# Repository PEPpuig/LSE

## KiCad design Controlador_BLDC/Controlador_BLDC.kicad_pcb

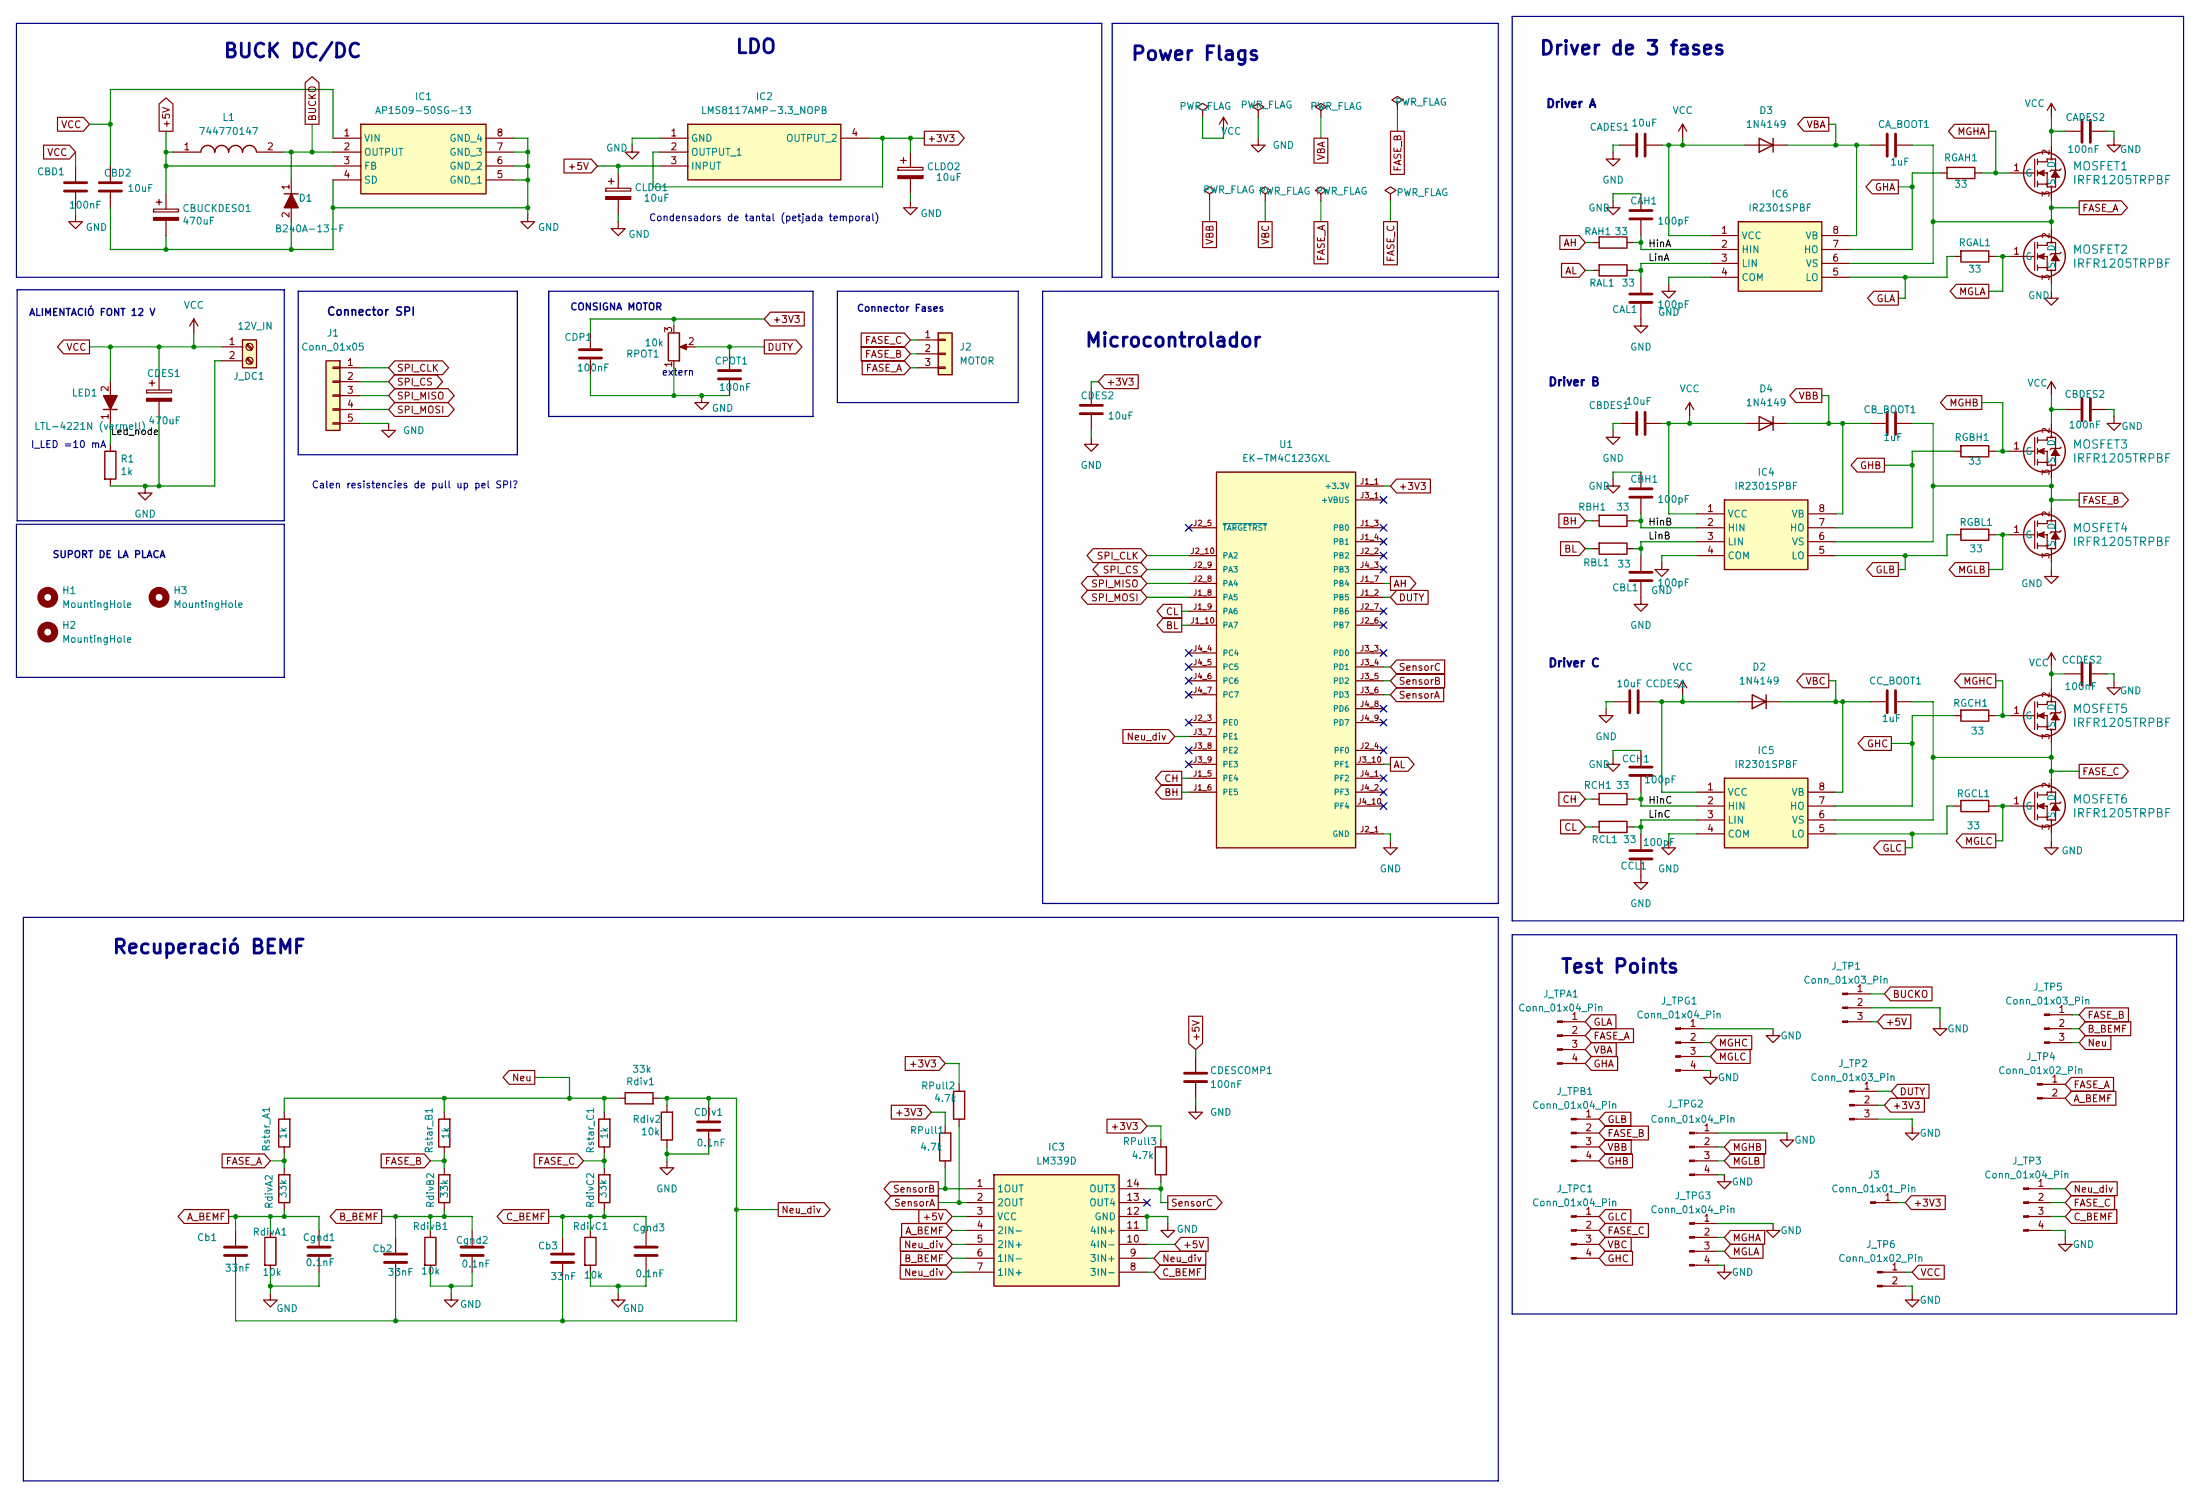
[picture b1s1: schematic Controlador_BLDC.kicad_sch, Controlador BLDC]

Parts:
CADES1: 10uF; C_1206_3216Metric_Pad1.33x1.80mm_HandSolder
CADES2: 100nF; C_1206_3216Metric_Pad1.33x1.80mm_HandSolder
CAH1: 100pF; C_1206_3216Metric_Pad1.33x1.80mm_HandSolder
CAL1: 100pF; C_1206_3216Metric_Pad1.33x1.80mm_HandSolder
CA_BOOT1: 1uF; C_1206_3216Metric_Pad1.33x1.80mm_HandSolder
CBD1: 100nF; C_1206_3216Metric_Pad1.33x1.80mm_HandSolder
CBD2: 10uF; C_1206_3216Metric_Pad1.33x1.80mm_HandSolder
CBDES1: 10uF; C_1206_3216Metric_Pad1.33x1.80mm_HandSolder
CBDES2: 100nF; C_1206_3216Metric_Pad1.33x1.80mm_HandSolder
CBH1: 100pF; C_1206_3216Metric_Pad1.33x1.80mm_HandSolder
CBL1: 100pF; C_1206_3216Metric_Pad1.33x1.80mm_HandSolder
CBUCKDESO1: 470uF; CP_Elec_10x10.5
CB_BOOT1: 1uF; C_1206_3216Metric_Pad1.33x1.80mm_HandSolder
CCDES1: 10uF; C_1206_3216Metric_Pad1.33x1.80mm_HandSolder
CCDES2: 100nF; C_1206_3216Metric_Pad1.33x1.80mm_HandSolder
CCH1: 100pF; C_1206_3216Metric_Pad1.33x1.80mm_HandSolder
CCL1: 100pF; C_1206_3216Metric_Pad1.33x1.80mm_HandSolder
CC_BOOT1: 1uF; C_1206_3216Metric_Pad1.33x1.80mm_HandSolder
CDES1: 470uF; CP_Elec_10x10.5
CDES2: 10uF; C_1206_3216Metric_Pad1.33x1.80mm_HandSolder
CDESCOMP1: 100nF; C_1206_3216Metric_Pad1.33x1.80mm_HandSolder
CDP1: 100nF; C_1206_3216Metric_Pad1.33x1.80mm_HandSolder
CDiv1: 0.1nF; C_1206_3216Metric_Pad1.33x1.80mm_HandSolder
CLDO1, CLDO2: 10uF; CP_EIA-2012-12_Kemet-R
CPOT1: 100nF; C_1206_3216Metric_Pad1.33x1.80mm_HandSolder
Cb1, Cb2, Cb3: 33nF; C_1206_3216Metric_Pad1.33x1.80mm_HandSolder
Cgnd1, Cgnd2, Cgnd3: 0.1nF; C_1206_3216Metric_Pad1.33x1.80mm_HandSolder
D1: B240A-13-F; DIOM5226X230N; Mouser Part Number 621-B240A-F
D2, D3, D4: 1N4149; D_DO-35_SOD27_P7.62mm_Horizontal
H1, H2, H3: MountingHole; MountingHole_3.2mm_M3
IC1: AP1509-50SG-13; SOIC127P600X170-8N; Manufacturer_Part_Number AP1509-50SG-13; Mouser Part Number 621-AP1509-50SG-13
IC2: LMS8117AMP-3.3_NOPB; SOT230P700X180-4N; Mouser Part Number 926-LMS8117AMP33NOPB
IC3: LM339D; SOIC127P600X175-14N; Mouser Part Number 595-LM339D
IC4, IC5, IC6: IR2301SPBF; SOIC127P600X175-8N; Mouser Part Number 942-IR2301SPBF
J1: Conn_01x05; PinHeader_1x05_P2.54mm_Vertical
J2: MOTOR; TerminalBlock_Phoenix_MKDS-1,5-3-5.08_1x03_P5.08mm_Horizont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
J3: Conn_01x01_Pin; PinHeader_1x01_P2.54mm_Vertical
J_DC1: 12V_IN; TerminalBlock_Phoenix_MKDS-1,5-2-5.08_1x02_P5.08mm_Horizont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
J_TP1, J_TP2, J_TP5: Conn_01x03_Pin; PinHeader_1x03_P2.54mm_Vertical
J_TP3: Conn_01x04_Pin; PinHeader_1x04_P2.54mm_Vertical
J_TP4, J_TP6: Conn_01x02_Pin; PinHeader_1x02_P2.54mm_Vertical
J_TPA1: Conn_01x04_Pin; PinHeader_1x04_P2.54mm_Vertical
J_TPB1: Conn_01x04_Pin; PinHeader_1x04_P2.54mm_Vertical
J_TPC1: Conn_01x04_Pin; PinHeader_1x04_P2.54mm_Vertical
J_TPG1, J_TPG2, J_TPG3: Conn_01x04_Pin; PinHeader_1x04_P2.54mm_Vertical
L1: 744770147; WE-PD_1260_1245_1280_121054; Mouser Part Number 710-744770147
LED1: LTL-4221N (vermell); LTL4221N; Mouser Part Number 859-LTL-4221N
MOSFET1, MOSFET2, MOSFET3, MOSFET4, MOSFET5, MOSFET6: IRFR1205TRPBF; D-PAK_TO-252AA_INF
R1: 1k; R_1206_3216Metric_Pad1.30x1.75mm_HandSolder
RAH1: 33; R_1206_3216Metric_Pad1.30x1.75mm_HandSolder
RAL1: 33; R_1206_3216Metric_Pad1.30x1.75mm_HandSolder
RBH1: 33; R_1206_3216Metric_Pad1.30x1.75mm_HandSolder
RBL1: 33; R_1206_3216Metric_Pad1.30x1.75mm_HandSolder
RCH1: 33; R_1206_3216Metric_Pad1.30x1.75mm_HandSolder
RCL1: 33; R_1206_3216Metric_Pad1.30x1.75mm_HandSolder
RGAH1: 33; R_1206_3216Metric_Pad1.30x1.75mm_HandSolder
RGAL1: 33; R_1206_3216Metric_Pad1.30x1.75mm_HandSolder
RGBH1: 33; R_1206_3216Metric_Pad1.30x1.75mm_HandSolder
RGBL1: 33; R_1206_3216Metric_Pad1.30x1.75mm_HandSolder
RGCH1: 33; R_1206_3216Metric_Pad1.30x1.75mm_HandSolder
RGCL1: 33; R_1206_3216Metric_Pad1.30x1.75mm_HandSolder
RPOT1: 10k; TerminalBlock_Phoenix_MKDS-1,5-3-5.08_1x03_P5.08mm_Horizont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
RPull1, RPull2, RPull3: 4.7k; R_1206_3216Metric_Pad1.30x1.75mm_HandSolder
Rdiv1: 33k; R_1206_3216Metric_Pad1.30x1.75mm_HandSolder
Rdiv2: 10k; R_1206_3216Metric_Pad1.30x1.75mm_HandSolder
RdivA1: 10k; R_1206_3216Metric_Pad1.30x1.75mm_HandSolder
RdivA2: 33k; R_1206_3216Metric_Pad1.30x1.75mm_HandSolder
RdivB1: 10k; R_1206_3216Metric_Pad1.30x1.75mm_HandSolder
RdivB2: 33k; R_1206_3216Metric_Pad1.30x1.75mm_HandSolder
RdivC1: 10k; R_1206_3216Metric_Pad1.30x1.75mm_HandSolder
RdivC2: 33k; R_1206_3216Metric_Pad1.30x1.75mm_HandSolder
Rstar_A1: 1k; R_1206_3216Metric_Pad1.30x1.75mm_HandSolder
Rstar_B1: 1k; R_1206_3216Metric_Pad1.30x1.75mm_HandSolder
Rstar_C1: 1k; R_1206_3216Metric_Pad1.30x1.75mm_HandSolder
U1: EK-TM4C123GXL; MODULE_EK-TM4C123GXL_mofied; PARTREV April 2013

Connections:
+3V3: CDES2.1, CDP1.1, CLDO2.1, IC2.2 (OUTPUT_1), IC2.4 (OUTPUT_2), J3.1, J_TP2.2, RPOT1.3, RPull1.2, RPull2.2, RPull3.2, U1.J1_1 (+3.3V)
+5V: CBUCKDESO1.1, CDESCOMP1.1, CLDO1.1, IC1.3 (FB), IC2.3 (INPUT), IC3.3 (VCC), IC3.10 (4IN-), J_TP1.3, L1.1
/HinA: CAH1.2, IC6.2 (HIN), RAH1.1
/HinB: CBH1.2, IC4.2 (HIN), RBH1.1
/HinC: CCH1.2, IC5.2 (HIN), RCH1.1
/Led_node: LED1.1 (K), R1.1
/LinA: CAL1.1, IC6.3 (LIN), RAL1.1
/LinB: CBL1.1, IC4.3 (LIN), RBL1.1
/LinC: CCL1.1, IC5.3 (LIN), RCL1.1
AH: RAH1.2, U1.J1_7 (PB4)
AL: RAL1.2, U1.J3_10 (PF1)
A_BEMF: Cb1.1, Cgnd1.1, IC3.4 (2IN-), J_TP4.2, RdivA1.1, RdivA2.1
BH: RBH1.2, U1.J1_6 (PE5)
BL: RBL1.2, U1.J1_10 (PA7)
BUCKO: D1.1 (K), IC1.2 (OUTPUT), J_TP1.1, L1.2
B_BEMF: Cb2.1, Cgnd2.1, IC3.6 (1IN-), J_TP5.2, RdivB1.1, RdivB2.1
CH: RCH1.2, U1.J1_5 (PE4)
CL: RCL1.2, U1.J1_9 (PA6)
C_BEMF: Cb3.1, Cgnd3.1, IC3.8 (3IN-), J_TP3.3, RdivC1.1, RdivC2.1
DUTY: CPOT1.1, J_TP2.1, RPOT1.2, U1.J1_2 (PB5)
FASE_A: CA_BOOT1.1, IC6.6 (VS), J2.3, J_TP4.1, J_TPA1.2, MOSFET1.3 (S), MOSFET2.2 (D), RdivA2.2, Rstar_A1.1
FASE_B: CB_BOOT1.1, IC4.6 (VS), J2.2, J_TP5.1, J_TPB1.2, MOSFET3.3 (S), MOSFET4.2 (D), RdivB2.2, Rstar_B1.1
FASE_C: CC_BOOT1.1, IC5.6 (VS), J2.1, J_TP3.2, J_TPC1.2, MOSFET5.3 (S), MOSFET6.2 (D), RdivC2.2, Rstar_C1.1
GHA: IC6.7 (HO), J_TPA1.4, RGAH1.2
GHB: IC4.7 (HO), J_TPB1.4, RGBH1.2
GHC: IC5.7 (HO), J_TPC1.4, RGCH1.2
GLA: IC6.5 (LO), J_TPA1.1, RGAL1.2
GLB: IC4.5 (LO), J_TPB1.1, RGBL1.2
GLC: IC5.5 (LO), J_TPC1.1, RGCL1.2
GND: CADES1.1, CADES2.2, CAH1.1, CAL1.2, CBD1.2, CBD2.2, CBDES1.1, CBDES2.2, CBH1.1, CBL1.2, CBUCKDESO1.2, CCDES1.2, CCDES2.2, CCH1.1, CCL1.2, CDES1.2, CDES2.2, CDESCOMP1.2, CDP1.2, CDiv1.2, CLDO1.2, CLDO2.2, CPOT1.2, Cgnd1.2, Cgnd2.2, Cgnd3.2, D1.2 (A), IC1.4 (SD), IC1.5 (GND_1), IC1.6 (GND_2), IC1.7 (GND_3), IC1.8 (GND_4), IC2.1 (GND), IC3.11 (4IN+), IC3.12 (GND), IC4.4 (COM), IC5.4 (COM), IC6.4 (COM), J1.5, J_DC1.2, J_TP1.2, J_TP2.3, J_TP3.4, J_TP6.2, J_TPG1.1, J_TPG1.4, J_TPG2.1, J_TPG2.4, J_TPG3.1, J_TPG3.4, MOSFET2.3 (S), MOSFET4.3 (S), MOSFET6.3 (S), R1.2, RPOT1.1, Rdiv2.1, RdivA1.2, RdivB1.2, RdivC1.2, U1.J2_1 (GND), U1.J3_2 (GND)
MGHA: J_TPG3.2, MOSFET1.1 (G), RGAH1.1
MGHB: J_TPG2.2, MOSFET3.1 (G), RGBH1.1
MGHC: J_TPG1.2, MOSFET5.1 (G), RGCH1.1
MGLA: J_TPG3.3, MOSFET2.1 (G), RGAL1.1
MGLB: J_TPG2.3, MOSFET4.1 (G), RGBL1.1
MGLC: J_TPG1.3, MOSFET6.1 (G), RGCL1.1
Neu: J_TP5.3, Rdiv1.1, Rstar_A1.2, Rstar_B1.2, Rstar_C1.2
Neu_div: CDiv1.1, Cb1.2, Cb2.2, Cb3.2, IC3.5 (2IN+), IC3.7 (1IN+), IC3.9 (3IN+), J_TP3.1, Rdiv1.2, Rdiv2.2, U1.J3_7 (PE1)
SPI_CLK: J1.1, U1.J2_10 (PA2)
SPI_CS: J1.2, U1.J2_9 (PA3)
SPI_MISO: J1.3, U1.J2_8 (PA4)
SPI_MOSI: J1.4, U1.J1_8 (PA5)
SensorA: IC3.2 (2OUT), RPull2.1, U1.J3_6 (PD3)
SensorB: IC3.1 (1OUT), RPull1.1, U1.J3_5 (PD2)
SensorC: IC3.14 (OUT3), RPull3.1, U1.J3_4 (PD1)
VBA: CA_BOOT1.2, D3.1 (K), IC6.8 (VB), J_TPA1.3
VBB: CB_BOOT1.2, D4.1 (K), IC4.8 (VB), J_TPB1.3
VBC: CC_BOOT1.2, D2.1 (K), IC5.8 (VB), J_TPC1.3
VCC: CADES1.2, CADES2.1, CBD1.1, CBD2.1, CBDES1.2, CBDES2.1, CCDES1.1, CCDES2.1, CDES1.1, D2.2 (A), D3.2 (A), D4.2 (A), IC1.1 (VIN), IC4.1 (VCC), IC5.1 (VCC), IC6.1 (VCC), J_DC1.1, J_TP6.1, LED1.2 (A), MOSFET1.2 (D), MOSFET3.2 (D), MOSFET5.2 (D)

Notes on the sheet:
I_LED =10 mA
Driver C
BUCK DC/DC
LDO
Calen resistencies de pull up pel SPI?
Connector Fases
Condensadors de tantal (petjada temporal)
Test Points
Driver de 3 fases
Driver A
Connector SPI
Recuperació BEMF
Driver B
Microcontrolador
ALIMENTACIÓ FONT 12 V
CONSIGNA MOTOR
extern
Power Flags
SUPORT DE LA PLACA

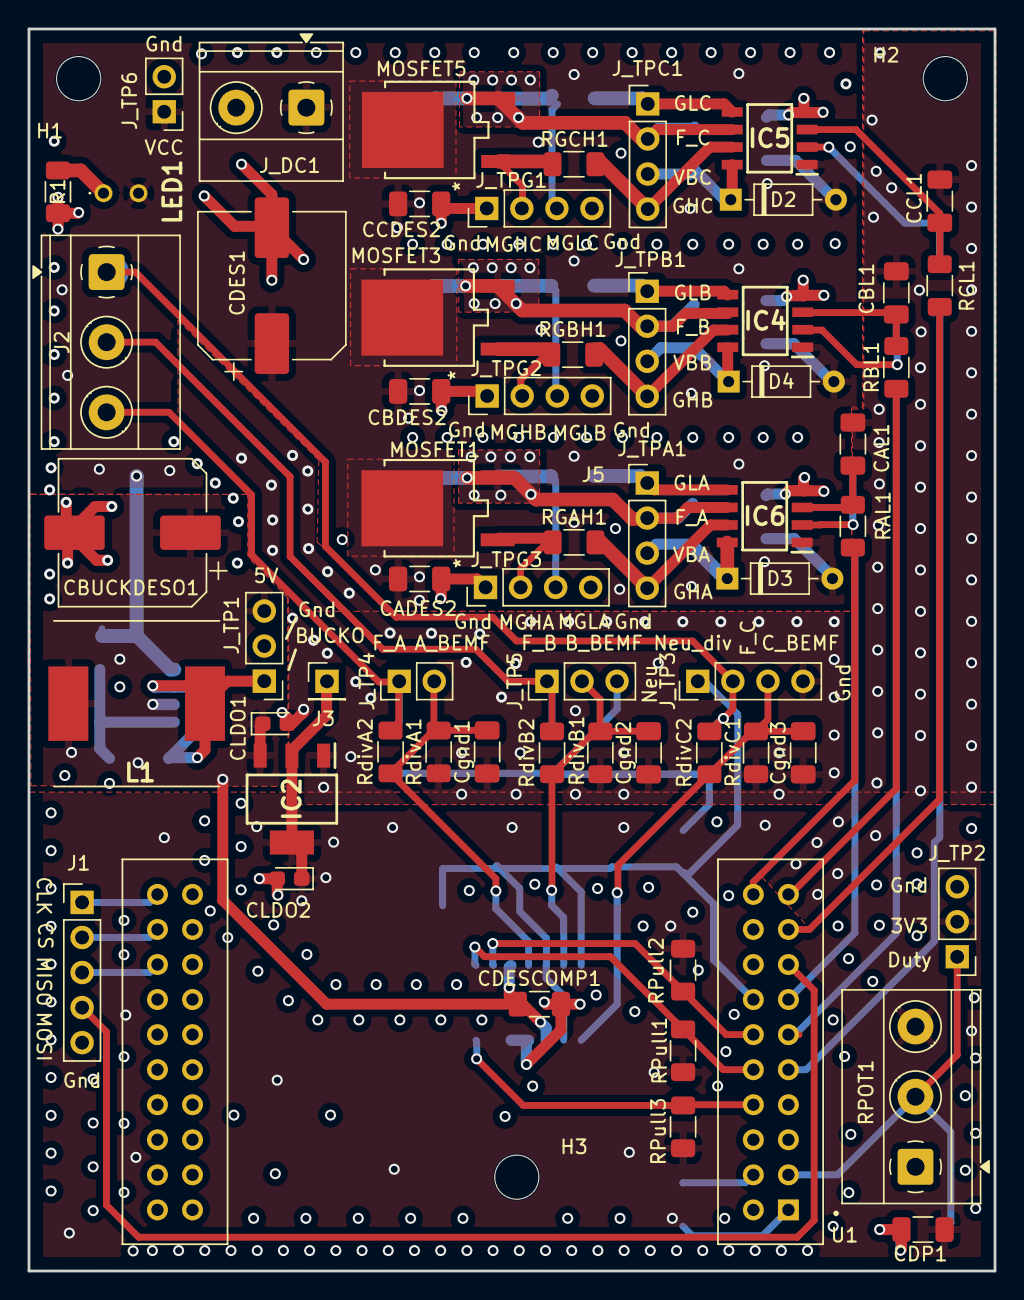
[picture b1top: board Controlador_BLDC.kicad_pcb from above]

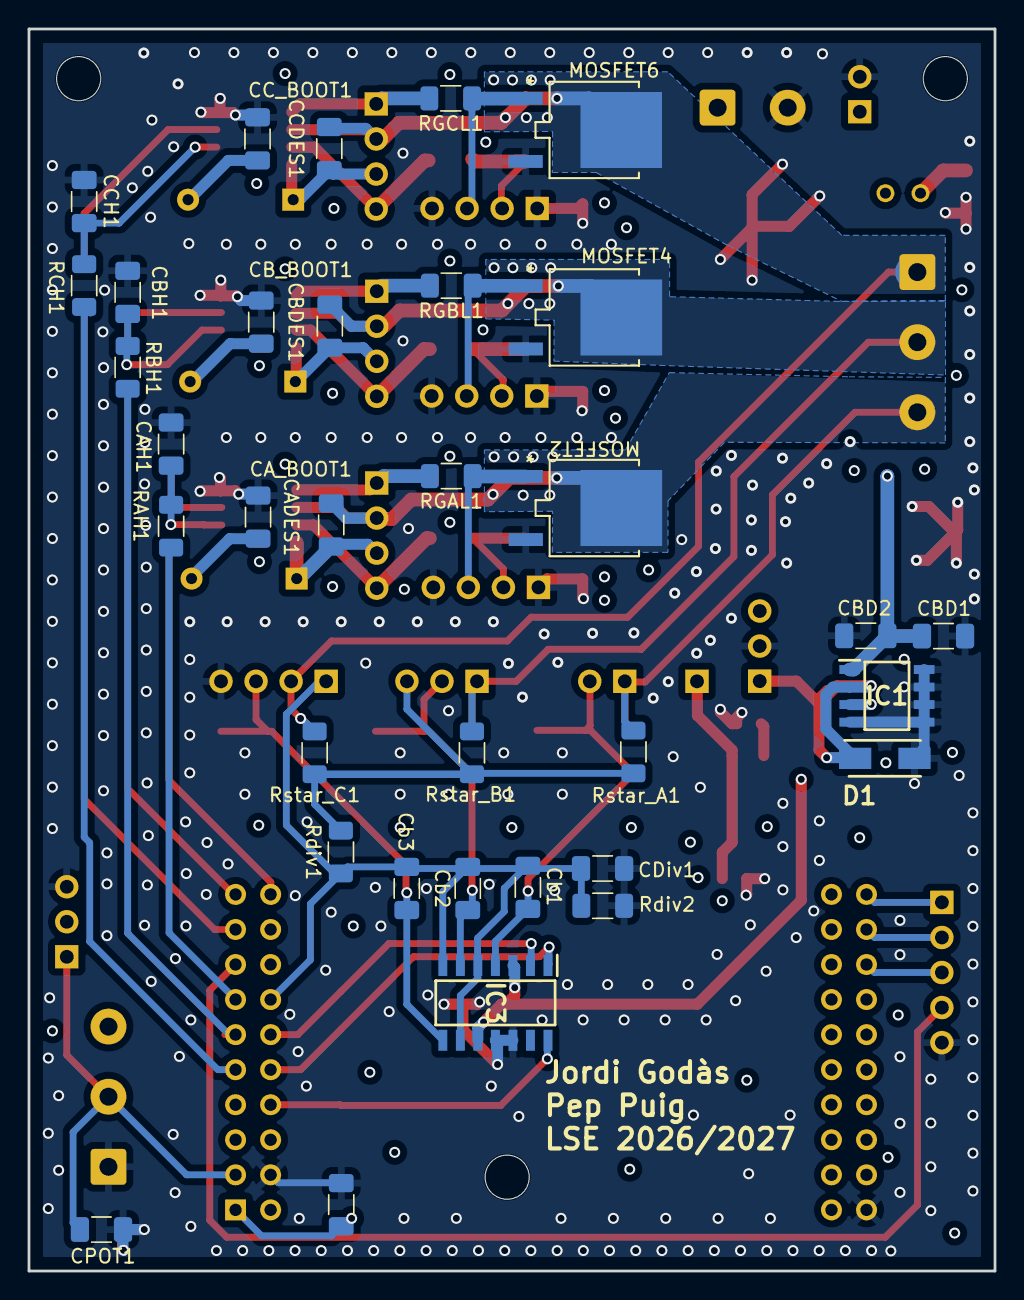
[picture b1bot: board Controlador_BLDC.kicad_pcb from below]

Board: 4 copper layers, 70.0 x 90.0 mm, 98 parts (34 on the bottom side), 49 nets.
